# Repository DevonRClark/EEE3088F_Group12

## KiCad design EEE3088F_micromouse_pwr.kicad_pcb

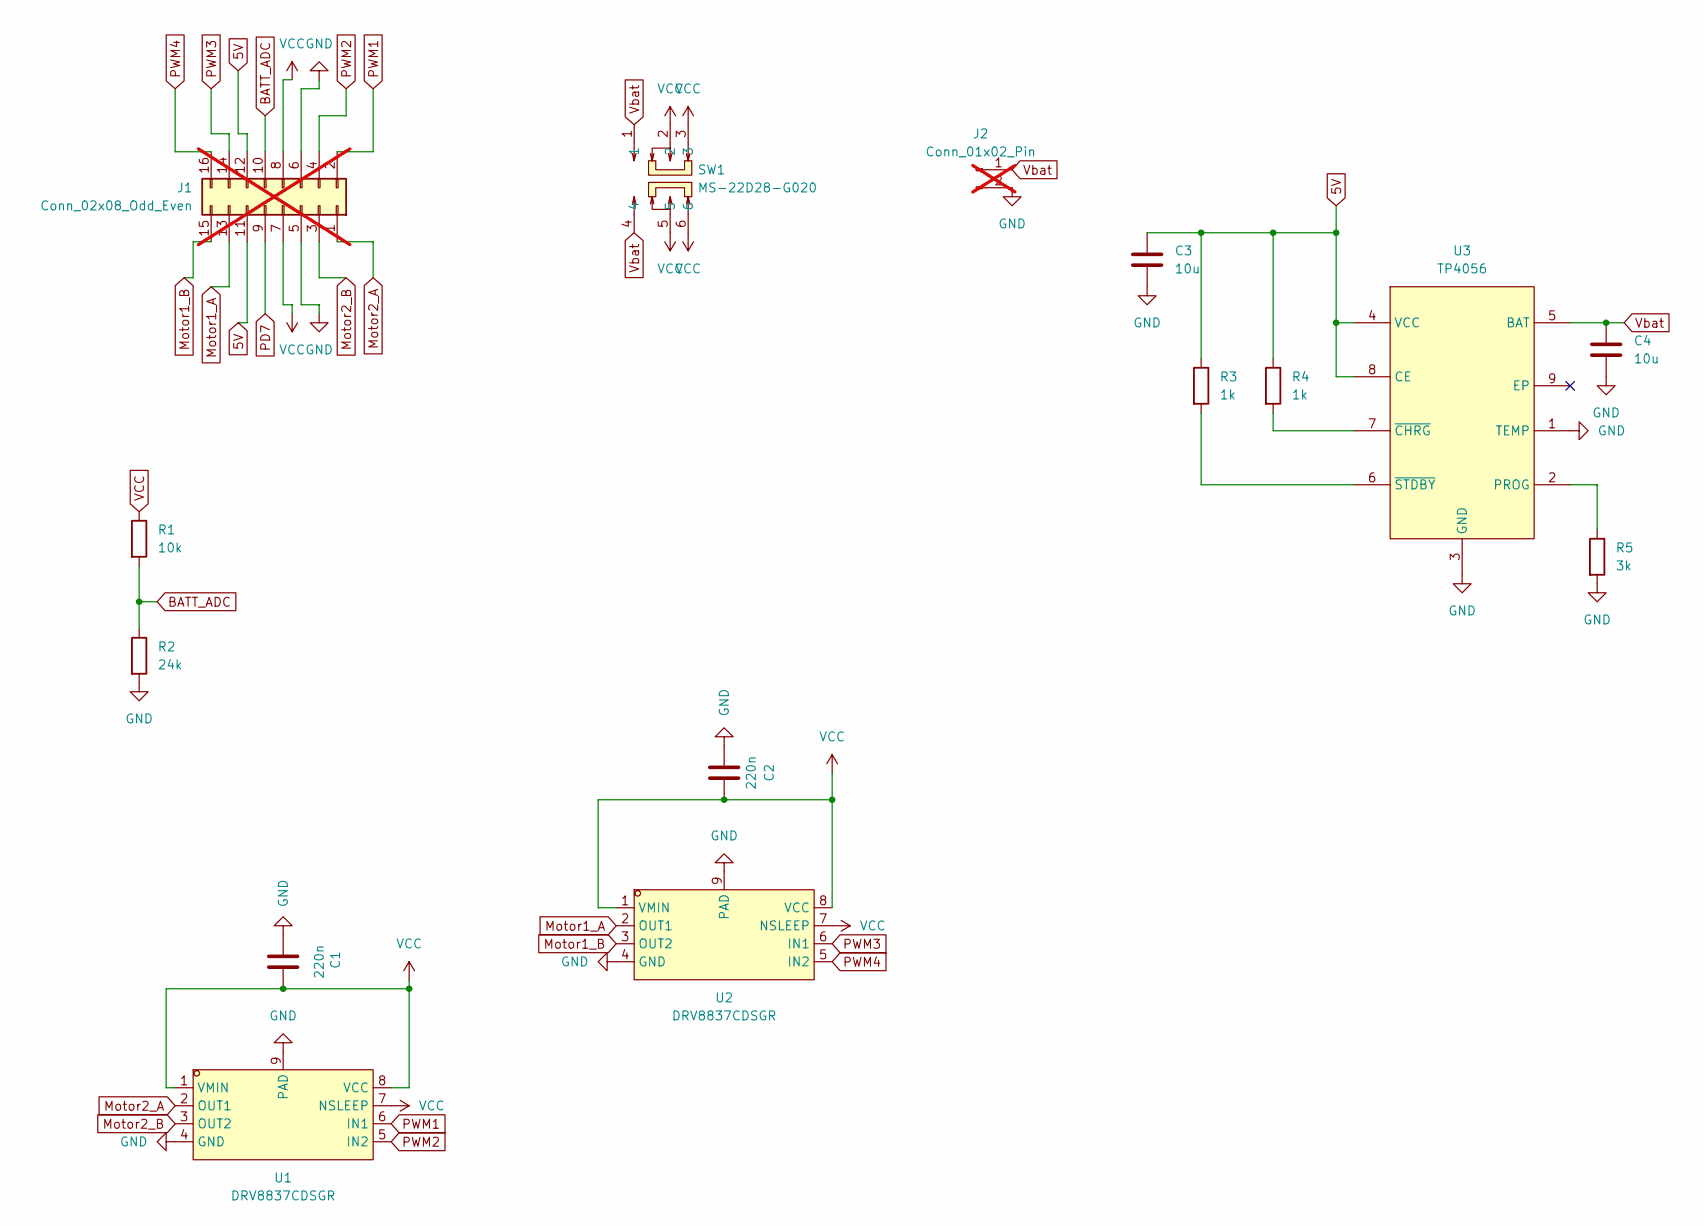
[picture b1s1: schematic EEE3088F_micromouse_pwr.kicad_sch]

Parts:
C1, C2: 220n; C_0603_1608Metric
C3, C4: 10u; C_0603_1608Metric
J1: Conn_02x08_Odd_Even; PinHeader_2x08_P2.54mm_Vertical; not fitted
J2: Conn_01x02_Pin; JST_PH_S2B-PH-K_1x02_P2.00mm_Horizontal; not fitted
R1: 10k; R_0805_2012Metric
R2: 24k; R_0805_2012Metric
R3, R4: 1k; R_0805_2012Metric
R5: 3k; R_0805_2012Metric
SW1: MS-22D28-G020; SW-SMD_MS-22D28-G020; LCSC Part C963205
U1, U2: DRV8837CDSGR; WSON-8_L2.0-W2.0-P0.50-TL-EP; LCSC Part C191000
U3: TP4056; ESOP-8_L4.9-W3.9-P1.27-LS6.0-BL-EP; LCSC Part C16581

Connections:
5V: C3.1, J1.11, J1.12, R3.1, R4.1, U3.4 (VCC), U3.8 (CE)
BATT_ADC: J1.10, R1.2, R2.1
GND: C1.1, C2.1, C3.2, C4.2, J1.5, J1.6, J2.2, R2.2, R5.2, U1.4 (GND), U1.9 (PAD), U2.4 (GND), U2.9 (PAD), U3.1 (TEMP), U3.3 (GND)
Motor1_A: J1.13, U2.2 (OUT1)
Motor1_B: J1.15, U2.3 (OUT2)
Motor2_A: J1.1, U1.2 (OUT1)
Motor2_B: J1.3, U1.3 (OUT2)
unnamed: R5.1, U3.2 (PROG)
unnamed: R4.2, U3.7 (~CHRG)
unnamed: R3.2, U3.6 (~STDBY)
PD7: J1.9
PWM1: J1.2, U1.6 (IN1)
PWM2: J1.4, U1.5 (IN2)
PWM3: J1.14, U2.6 (IN1)
PWM4: J1.16, U2.5 (IN2)
VCC: C1.2, C2.2, J1.7, J1.8, R1.1, SW1.2, SW1.3, SW1.5, SW1.6, U1.1 (VMIN), U1.7 (NSLEEP), U1.8 (VCC), U2.1 (VMIN), U2.7 (NSLEEP), U2.8 (VCC)
Vbat: C4.1, J2.1, SW1.1, SW1.4, U3.5 (BAT)

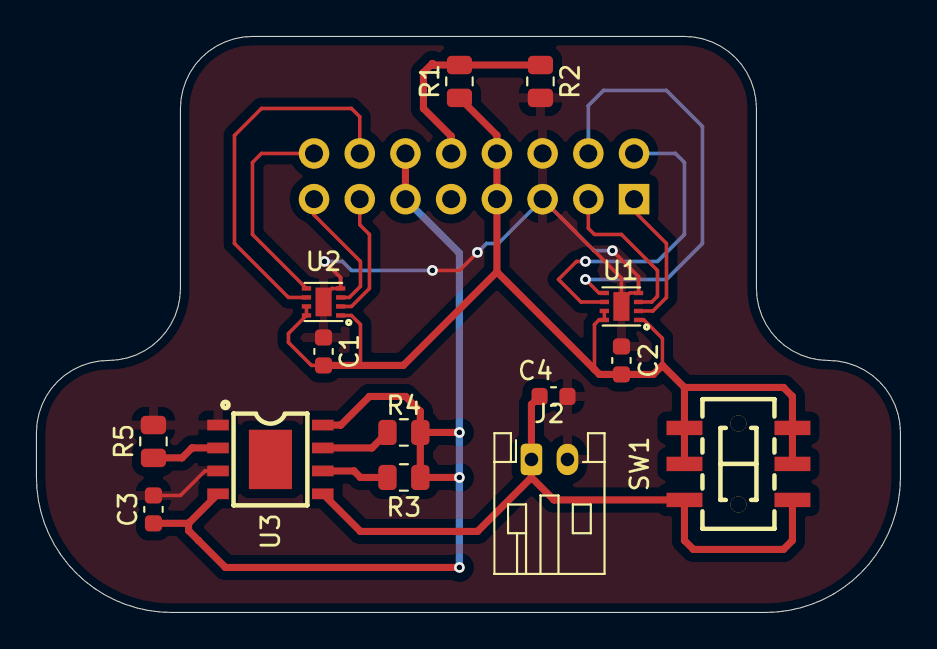
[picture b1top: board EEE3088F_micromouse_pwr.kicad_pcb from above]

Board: 2 copper layers, 48.0 x 32.0 mm, 15 parts (1 on the bottom side), 16 nets.

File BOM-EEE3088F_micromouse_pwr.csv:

Comment,Designator,Footprint,LCSC
TP4056,U3,ESOP-8_L4.9-W3.9-P1.27-LS6.0-BL-EP,C16581
DRV8837CDSGR,"U1,U2",WSON-8_L2.0-W2.0-P0.50-TL-EP,C191000
MS-22D28-G020,SW1,SW-SMD_MS-22D28-G020,C963205
24k,R2,R_0805_2012Metric,
10k,R1,R_0805_2012Metric,
3k,R5,R_0805_2012Metric,
1k,R4,R_0805_2012Metric,
1k,R3,R_0805_2012Metric,
220n,C2,C_0603_1608Metric,
220n,C1,C_0603_1608Metric,
10u,C4,C_0603_1608Metric,
10u,C3,C_0603_1608Metric,

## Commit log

2024-04-11 Add files via upload
    Production files:
    -A zipped file containing the Gerbers
    -The Bill of Materials (BOM) .csv file
    -The POS/CPL .csv file
    Screenshots of:
    -BOM page
2024-04-17 KiCad project files
2024-04-18 Gerber files
2024-04-18 production files
2024-04-18 Backups
2024-04-18 Project description
